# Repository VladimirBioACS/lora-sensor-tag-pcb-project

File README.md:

# LoRa Sensor TAG

Simple LoRa humidity and temperature monitoring device, based on the ESP32-Wroom-D SoC module.
Repo contains KiCAD 10 project for LoRa Sensor TAG device with external component libs.

## Project description

The architecture of the project is described with the diagram below (lora_sensor_tag_architecture.jpg):

The LoRa Sensor Project is designed to create a network of low-power, long-range sensors for environmental monitoring. 
The project aims to leverage LoRa technology to enable efficient data collection from remote locations, 
providing real-time insights into various environmental parameters such as temperature and humidity. The LoRa modem works
within 433 Mhz LF baseband.

It is developed simply for the educational purpose, aiming to provide students and hobbyists with hands-on experience in 
building and managing a LoRa-based sensor network.

The device composed of several key components:

- A LoRa module for long-range wireless communication.
- Sensor for measuring environmental parameters such as temperature and humidity.
- A microcontroller to process sensor data and manage communication.
- A power source (li-ion battery) with DC-DC buck-boost converter and LDO to manage power supply and ensure stable operation.
- Auxiliary components such as USB-UART bridge for serial communication and programming the microcontroller.

The following key components were used:

- MAX17048G_T10 - Fuel Gauge IC to monitor battery status
- MCP73871-2CAI_ML - Li-Ion/Li-Polymer Battery Charger to manage battery charging and protection
- SHT20 - Temperature and Humidity Sensor to measure environmental conditions
- SX1276IMLTRT - LoRa Transceiver Module to enable long-range wireless communication
- PE4259 - RF switch for LoRa antenna
- TPS63070RNMR - Buck-Boost Converter to manage power supply and ensure stable operation
- ESP32 - Microcontroller to process sensor data and manage communication
- CP2102 - USB to UART Bridge Controller to enable serial communication between the microcontroller and a computer. Also, acts as a programmer for the microcontroller.

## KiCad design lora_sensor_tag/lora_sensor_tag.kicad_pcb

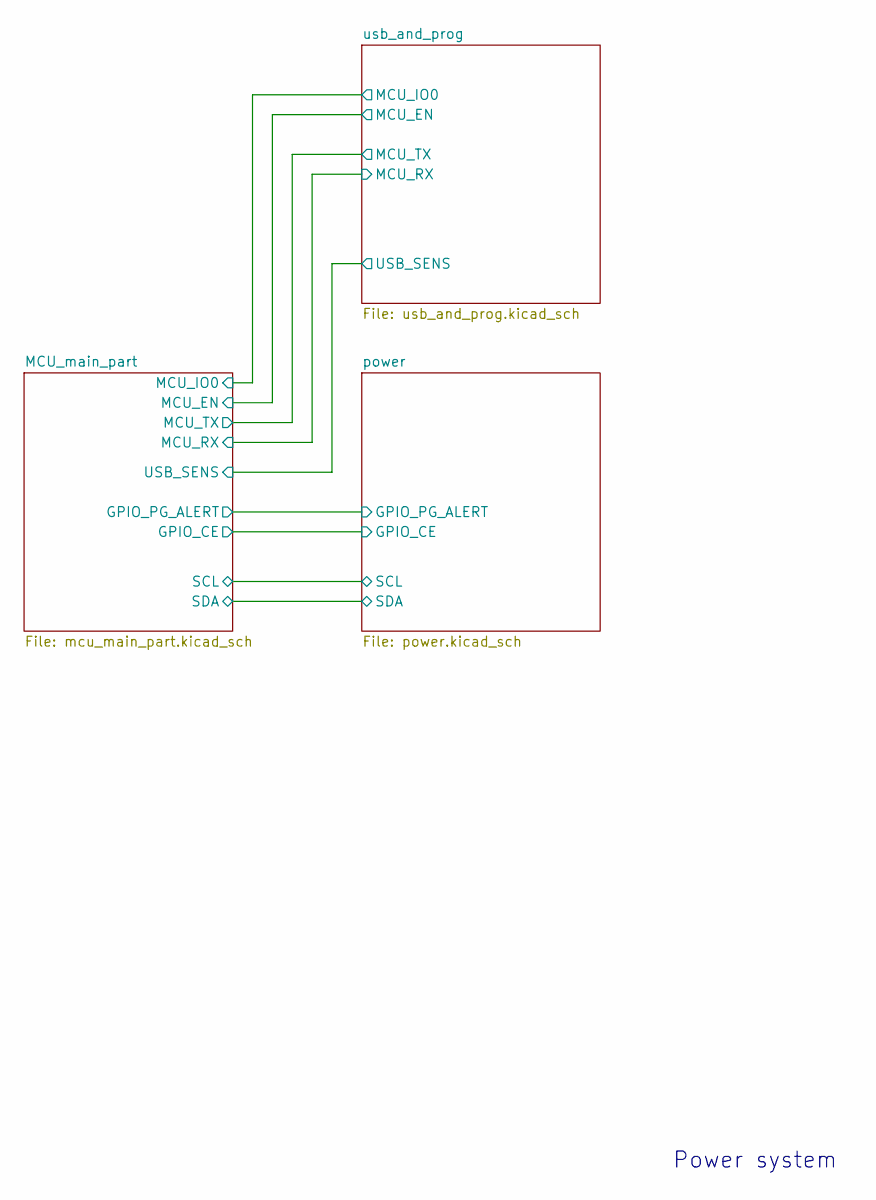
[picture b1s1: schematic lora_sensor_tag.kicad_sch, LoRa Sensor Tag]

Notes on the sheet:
Power system

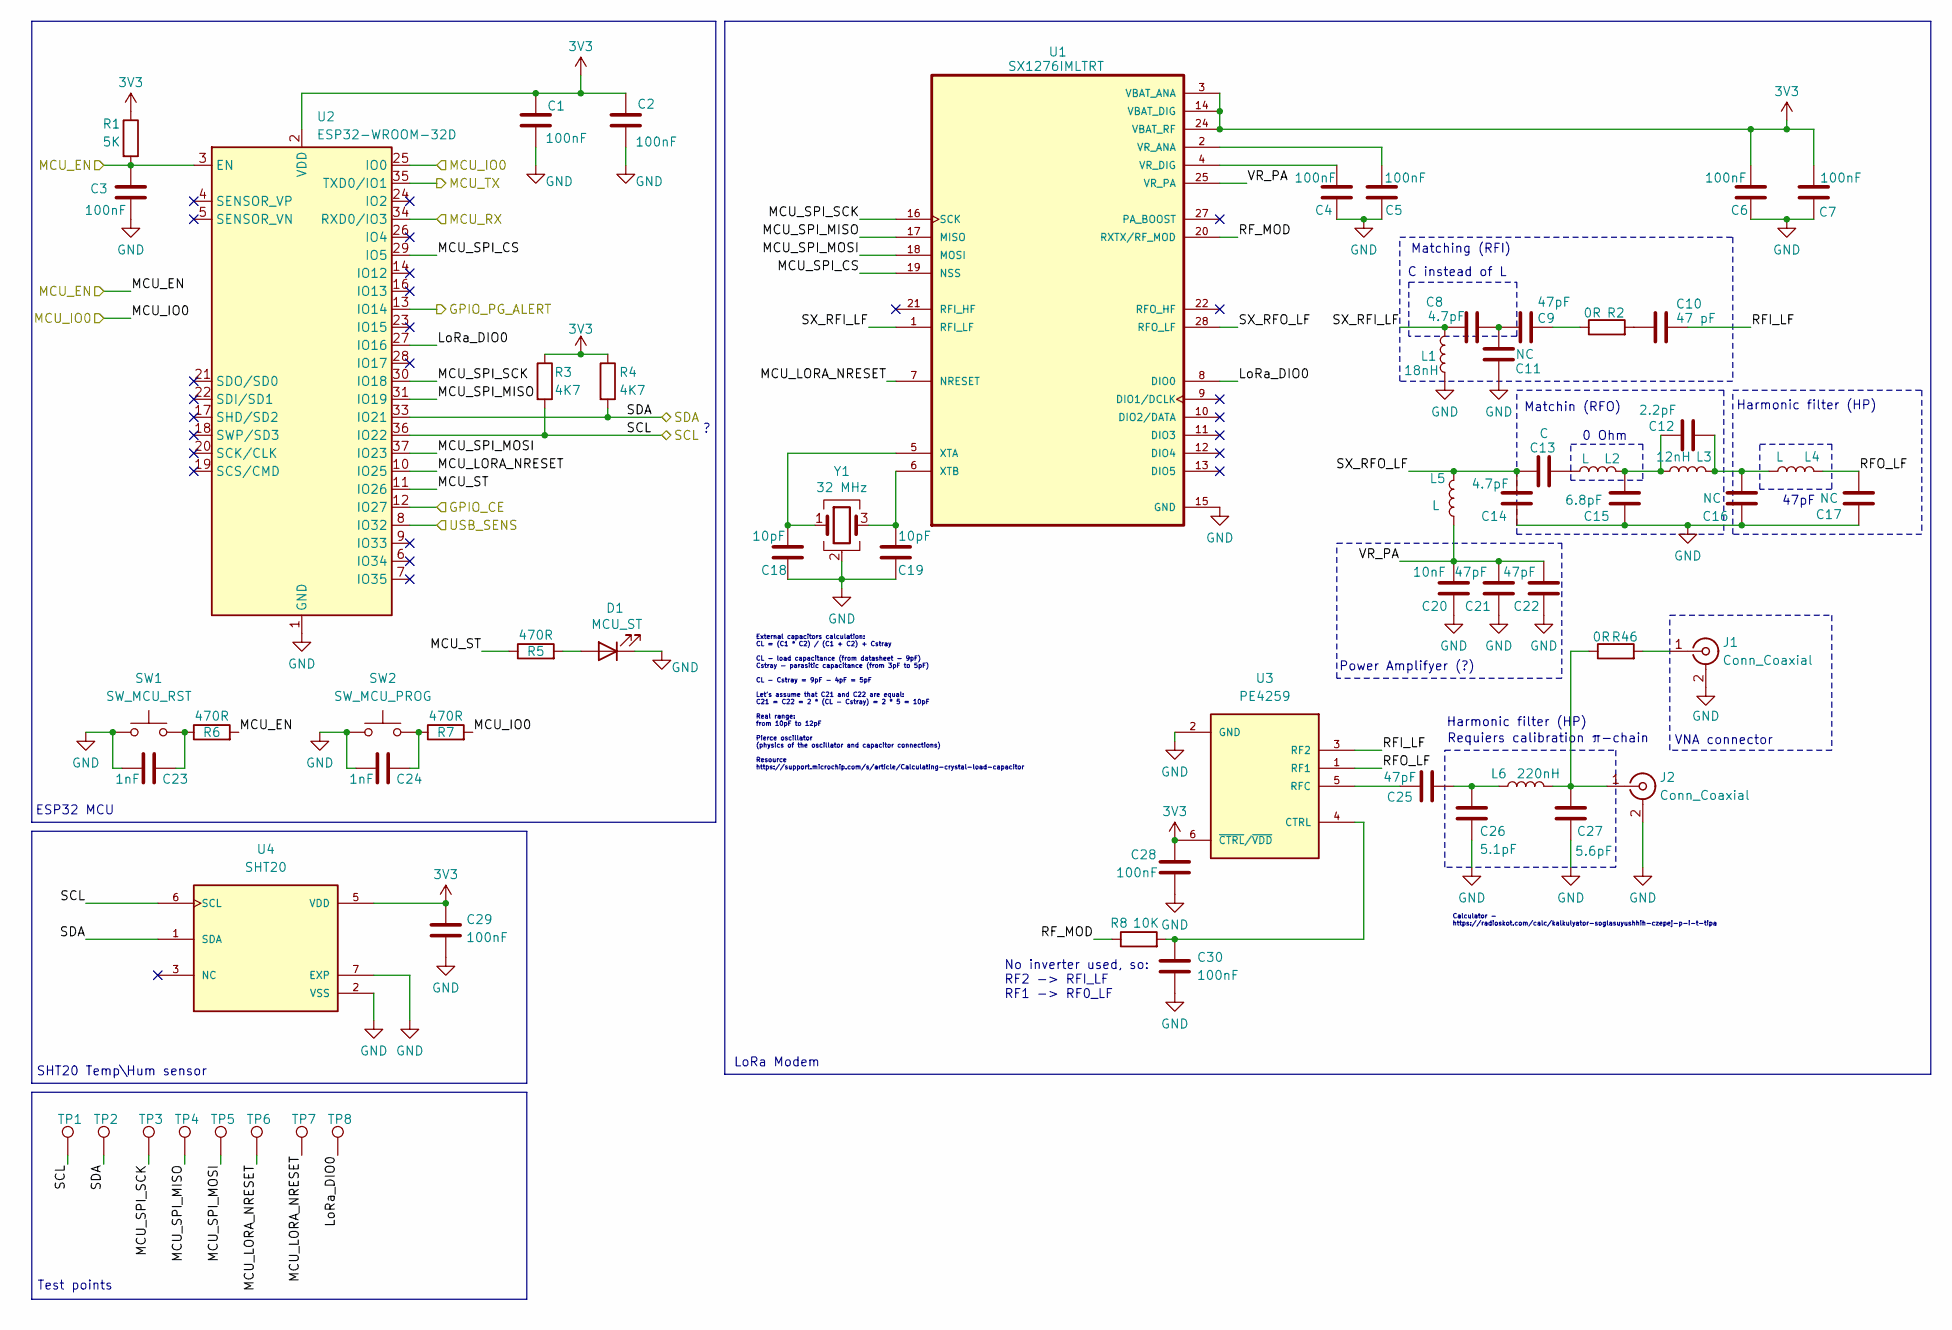
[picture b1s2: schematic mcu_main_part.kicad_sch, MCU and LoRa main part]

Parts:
C1, C2, C3, C4, C5, C6, C7, C28, C29, C30: 100nF; C_0603_1608Metric
C8, C14: 4.7pF; C_0402_1005Metric
C9, C21, C22, C25: 47pF; C_0402_1005Metric
C10: 47 pF; C_0402_1005Metric
C11, C16, C17: NC; C_0402_1005Metric
C12: 2.2pF; C_0402_1005Metric
C13: C; C_0402_1005Metric
C15: 6.8pF; C_0402_1005Metric
C18, C19: 10pF; C_0603_1608Metric
C20: 10nF; C_0402_1005Metric
C23, C24: 1nF; C_0603_1608Metric
C26: 5.1pF; C_0402_1005Metric
C27: 5.6pF; C_0402_1005Metric
D1: MCU_ST; LED_0603_1608Metric
J1, J2: Conn_Coaxial; SMA_BAT_Wireless_BWSMA-KWE-Z001
L1: 18nH; L_0402_1005Metric
L2: L; R_0402_1005Metric
L3: 12nH; L_0402_1005Metric
L4: L; C_0402_1005Metric
L5: L; L_0402_1005Metric
L6: 220nH; L_0402_1005Metric
R1: 5K; R_0603_1608Metric
R2: 0R; R_0603_1608Metric
R3, R4: 4K7; R_0603_1608Metric
R5, R6, R7: 470R; R_0603_1608Metric
R8: 10K; R_0603_1608Metric
R46: 0R; R_0402_1005Metric
SW1: SW_MCU_RST; SW_Push_1TS009xxxx-xxxx-xxxx_6x6x5mm
SW2: SW_MCU_PROG; SW_Push_1TS009xxxx-xxxx-xxxx_6x6x5mm
TP1, TP2, TP3, TP4, TP5, TP6, TP7, TP8: TestPoint; TestPoint_Pad_D1.0mm
U1: SX1276IMLTRT; QFN65P600X600X100-29N; PARTREV 5
U2: ESP32-WROOM-32D
U3: PE4259; SOT65P215X110-6N
U4: SHT20; XDCR_SHT20; PARTREV 4
Y1: 32 MHz; Crystal_SMD_3225-4Pin_3.2x2.5mm

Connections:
3V3: C1.1, C2.1, C6.1, C7.1, C28.1, C29.1, R1.1, R3.1, R4.1, U1.3 (VBAT_ANA), U1.14 (VBAT_DIG), U1.24 (VBAT_RF), U2.2 (VDD), U3.6 (~CTRL/~VDD), U4.5 (VDD); also elsewhere on the board
/MCU_main_part/GPIO_CE: U2.12 (IO27); also elsewhere on the board
/MCU_main_part/GPIO_PG_ALERT: U2.13 (IO14); also elsewhere on the board
/MCU_main_part/LoRa_DIO0: TP8.1 (1_1), U1.8 (DIO0), U2.27 (IO16)
/MCU_main_part/MCU_EN: C3.1, R1.2, R6.2, U2.3 (EN); also elsewhere on the board
/MCU_main_part/MCU_IO0: R7.2, U2.25 (IO0); also elsewhere on the board
/MCU_main_part/MCU_LORA_NRESET: TP6.1 (1_1), TP7.1 (1_1), U1.7 (NRESET), U2.10 (IO25)
/MCU_main_part/MCU_SPI_CS: U1.19 (NSS), U2.29 (IO5)
/MCU_main_part/MCU_SPI_MISO: TP4.1 (1_1), U1.17 (MISO), U2.31 (IO19)
/MCU_main_part/MCU_SPI_MOSI: TP5.1 (1_1), U1.18 (MOSI), U2.37 (IO23)
/MCU_main_part/MCU_SPI_SCK: TP3.1 (1_1), U1.16 (SCK), U2.30 (IO18)
/MCU_main_part/MCU_ST: R5.1, U2.11 (IO26)
/MCU_main_part/RFI_LF: C10.2, U3.3 (RF2)
/MCU_main_part/RFO_LF: C17.1, L4.2, U3.1 (RF1)
/MCU_main_part/RF_MOD: R8.1, U1.20 (RXTX/RF_MOD)
/MCU_main_part/SCL: R3.2, TP1.1 (1_1), U2.36 (IO22), U4.6 (SCL); also elsewhere on the board
/MCU_main_part/SDA: R4.2, TP2.1 (1_1), U2.33 (IO21), U4.1 (SDA); also elsewhere on the board
/MCU_main_part/SX_RFI_LF: C8.1, L1.2, U1.1 (RFI_LF)
/MCU_main_part/SX_RFO_LF: C13.2, C14.1, L5.2, U1.28 (RFO_LF)
/MCU_main_part/USB_SENS: U2.8 (IO32); also elsewhere on the board
/MCU_main_part/VR_PA: C20.1, C21.1, C22.1, L5.1, U1.25 (VR_PA)
/usb_and_prog/RX: U2.34 (RXD0/IO3); also elsewhere on the board
/usb_and_prog/TX: U2.35 (TXD0/IO1); also elsewhere on the board
GND: C1.2, C2.2, C3.2, C4.2, C5.2, C6.2, C7.2, C11.2, C14.2, C15.2, C16.2, C17.2, C18.2, C19.2, C20.2, C21.2, C22.2, C23.1, C24.1, C26.1, C27.1, C28.2, C29.2, C30.1, D1.1 (K), J1.2 (Ext), J2.2 (Ext), L1.1, SW1.1, SW2.1, U1.15 (GND), U1.23 (GND), U1.26 (GND), U1.29 (GND), U2.1 (GND), U2.15 (GND), U2.38 (GND), U2.39 (GND), U3.2 (GND), U4.2 (VSS), U4.7 (EXP), Y1.2 (G), Y1.4 (G); also elsewhere on the board
unnamed: C9.2, R2.1
unnamed: C10.1, R2.2
unnamed: C8.2, C9.1, C11.1
unnamed: C12.1, C16.1, L3.2, L4.1
unnamed: C12.2, C15.1, L2.2, L3.1
unnamed: C13.1, L2.1
unnamed: C23.2, R6.1, SW1.2
unnamed: C24.2, R7.1, SW2.2
unnamed: C25.2, C26.2, L6.1
unnamed: D1.2 (A), R5.2
unnamed: J1.1 (In), R46.2
unnamed: C27.2, J2.1 (In), L6.2, R46.1
unnamed: C5.1, U1.2 (VR_ANA)
unnamed: C4.1, U1.4 (VR_DIG)
unnamed: C18.1, U1.5 (XTA), Y1.1
unnamed: C19.1, U1.6 (XTB), Y1.3
unnamed: C30.2, R8.2, U3.4 (CTRL)
unnamed: C25.1, U3.5 (RFC)

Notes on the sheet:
SHT20 Temp\Hum sensor
External capacitors calculation: CL = (C1 * C2) / (C1 + C2) + Cstray CL - load capacitance (from datasheet - 9pF) Cstray - parasitic capacitance (from 3pF to 5pF) CL - Cstray = 9pF - 4pF = 5pF Let's assume that C21 and C22 are equal: C21 = C22 = 2 * (CL - Cstray) = 2 * 5 = 10pF Real range: from 10p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
Requiers calibration π-chain
Harmonic filter (HP)
Test points
LoRa Modem
ESP32 MCU
0 Ohm
Matchin (RFO)
47pF
VNA connector
C instead of L
Power Amplifyer (?)
Calculator - https://radioskot.com/calc/kalkulyator-soglasuyushhih-czepej-p-i-t-tipa
Matching (RFI)
No inverter used, so: RF2 -> RFI_LF RF1 -> RF0_LF

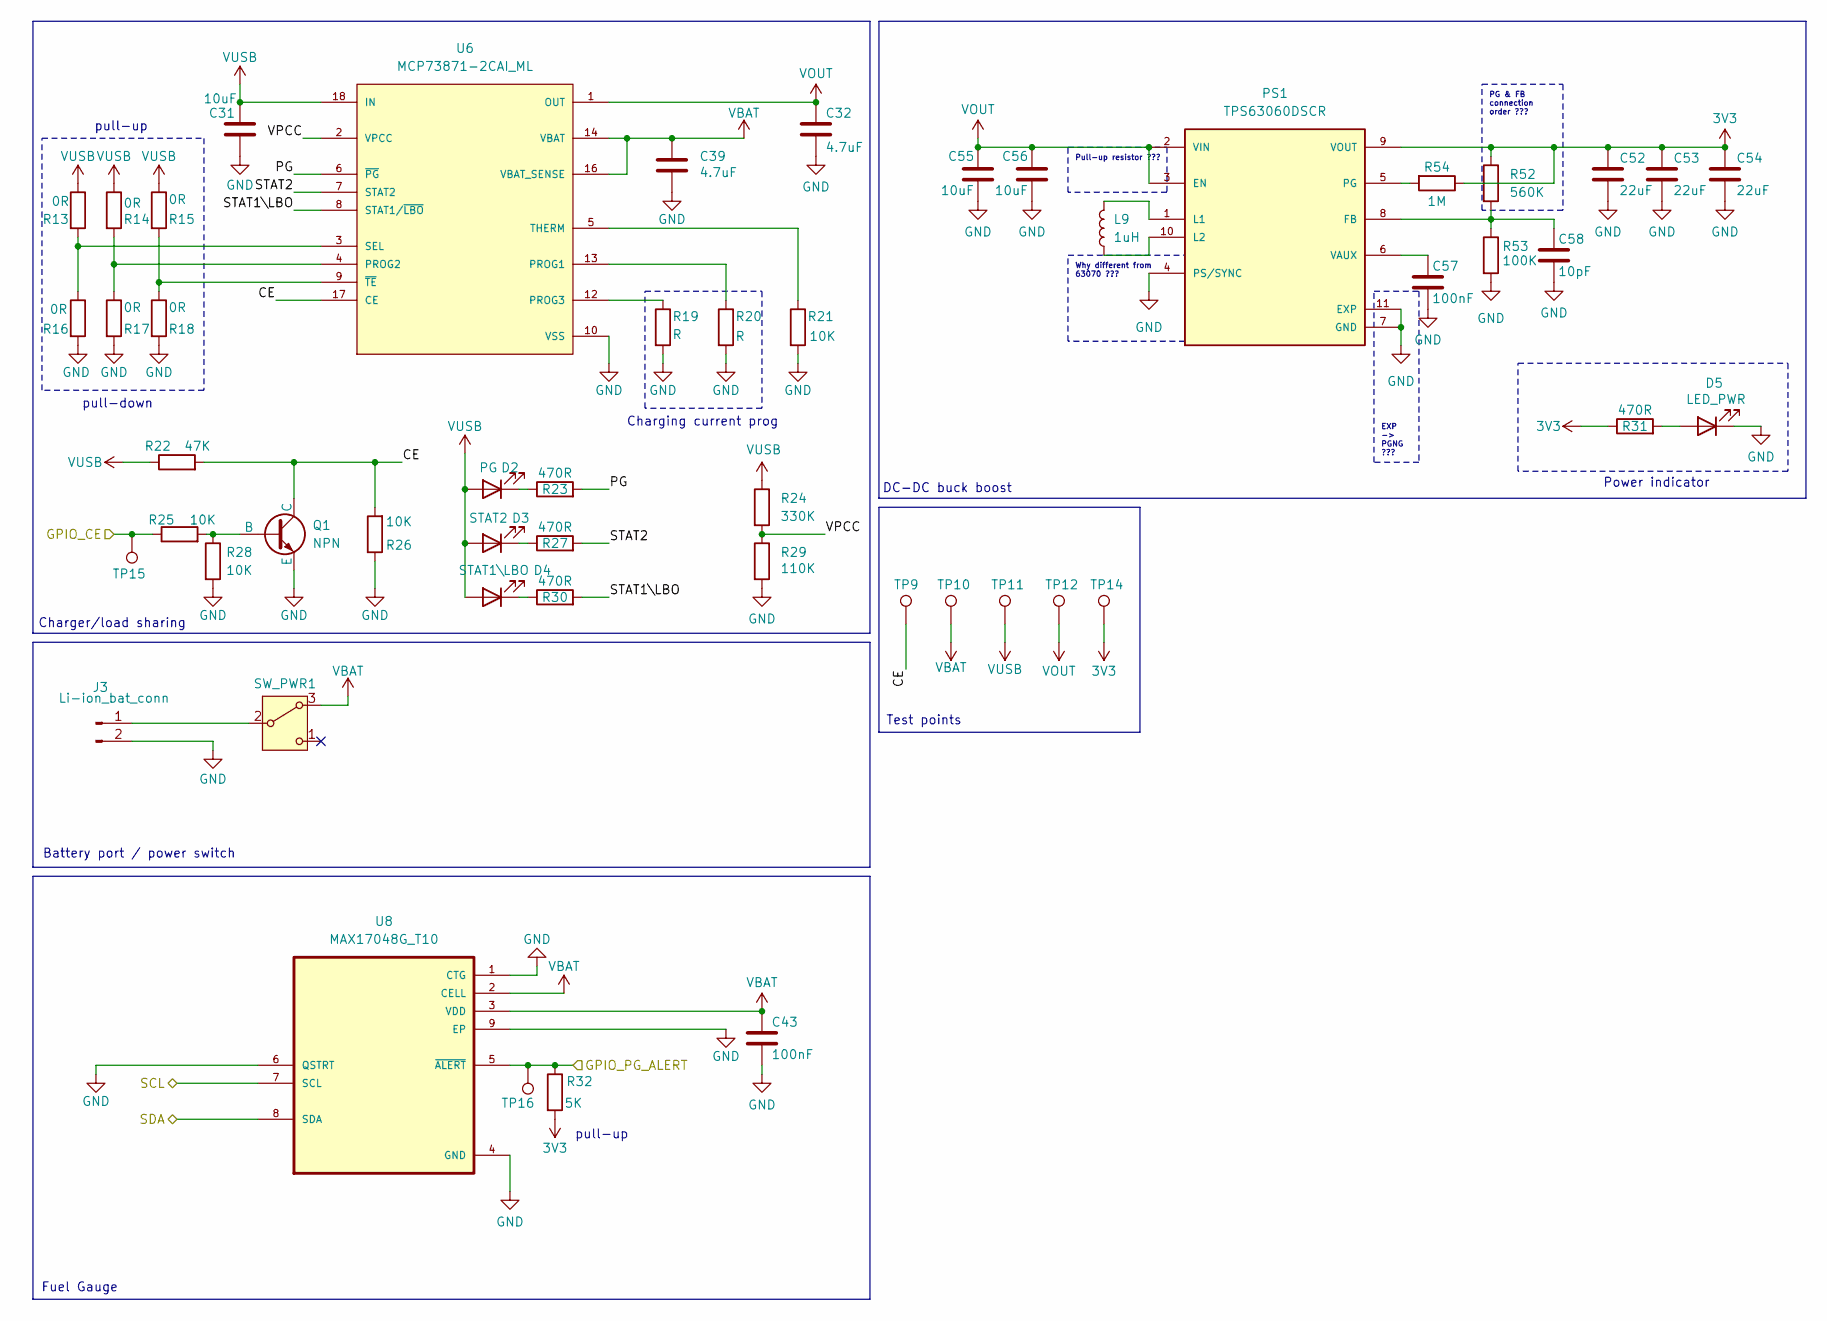
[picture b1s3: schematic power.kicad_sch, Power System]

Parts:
C31: 10uF; C_0603_1608Metric
C32, C39: 4.7uF; C_0603_1608Metric
C43: 100nF; C_0603_1608Metric
C52, C53, C54: 22uF; C_0805_2012Metric
C55, C56: 10uF; C_0805_2012Metric
C57: 100nF; C_0402_1005Metric
C58: 10pF; C_0603_1608Metric
D2: PG; LED_0603_1608Metric
D3: STAT2; LED_0603_1608Metric
D4: STAT1\LBO; LED_0603_1608Metric
D5: LED_PWR; LED_0603_1608Metric
J3: Li-ion_bat_conn; PinHeader_1x02_P2.54mm_Vertical
L9: 1uH; L_Coilcraft_XxL4020
PS1: TPS63060DSCR; CONV_TPS63060DSCR; PARTREV C
Q1: NPN; SOT-23
R13, R14, R15, R16, R17, R18: 0R; R_0603_1608Metric
R19, R20: R; R_0603_1608Metric
R21, R25, R26, R28: 10K; R_0603_1608Metric
R22: 47K; R_0603_1608Metric
R23, R27, R30, R31: 470R; R_0603_1608Metric
R24: 330K; R_0603_1608Metric
R29: 110K; R_0603_1608Metric
R32: 5K; R_0603_1608Metric
R52: 560K; R_0603_1608Metric
R53: 100K; R_0603_1608Metric
R54: 1M; R_0603_1608Metric
SW_PWR1: SW_Nidec_CAS-120A1; Nidec_Copal_CAS-120A
TP9, TP10, TP11, TP12, TP14, TP15, TP16: TestPoint; TestPoint_Pad_D1.0mm
U6: MCP73871-2CAI_ML; QFN50P400X400X100-21N; PARTREV D
U8: MAX17048G_T10; SON50P200X200X80-9N

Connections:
3V3: C52.1, C53.1, C54.1, PS1.9 (VOUT), R31.1, R32.2, R52.1, R54.1, TP14.1 (1_1); also elsewhere on the board
/MCU_main_part/GPIO_CE: R25.1, TP15.1 (1_1); also elsewhere on the board
/MCU_main_part/GPIO_PG_ALERT: R32.1, TP16.1 (1_1), U8.5 (~ALERT); also elsewhere on the board
/MCU_main_part/SCL: U8.7 (SCL); also elsewhere on the board
/MCU_main_part/SDA: U8.8 (SDA); also elsewhere on the board
/power/CE: Q1.1 (C), R22.2, R26.2, TP9.1 (1_1), U6.17 (CE)
/power/PG: R23.2, U6.6 (~PG)
/power/STAT1\LBO: R30.2, U6.8 (STAT1/~LBO)
/power/STAT2: R27.2, U6.7 (STAT2)
/power/VPCC: R24.2, R29.1, U6.2 (VPCC)
GND: C31.1, C32.2, C39.2, C43.2, C52.2, C53.2, C54.2, C55.2, C56.2, C57.2, C58.2, D5.1 (K), J3.2, PS1.4 (PS/SYNC), PS1.7 (GND), PS1.11 (EXP), Q1.3 (E), R16.2, R17.2, R18.2, R19.2, R20.2, R21.2, R26.1, R28.2, R29.2, R53.2, U6.10 (VSS), U6.11 (VSS), U6.21 (VSS), U8.1 (CTG), U8.4 (GND), U8.6 (QSTRT), U8.9 (EP); also elsewhere on the board
unnamed: D2.1 (K), R23.1
unnamed: D3.1 (K), R27.1
unnamed: D4.1 (K), R30.1
unnamed: D5.2 (A), R31.2
unnamed: J3.1, SW_PWR1.2 (B)
unnamed: C58.1, PS1.8 (FB), R52.2, R53.1
unnamed: L9.2, PS1.1 (L1)
unnamed: L9.1, PS1.10 (L2)
unnamed: PS1.5 (PG), R54.2
unnamed: C57.1, PS1.6 (VAUX)
unnamed: Q1.2 (B), R25.2, R28.1
unnamed: R20.1, U6.13 (PROG1)
unnamed: R14.2, R17.1, U6.4 (PROG2)
unnamed: R19.1, U6.12 (PROG3)
unnamed: R13.2, R16.1, U6.3 (SEL)
unnamed: R21.1, U6.5 (THERM)
unnamed: R15.2, R18.1, U6.9 (~TE)
VBAT: C39.1, C43.1, SW_PWR1.3 (A), TP10.1 (1_1), U6.14 (VBAT), U6.15 (VBAT), U6.16 (VBAT_SENSE), U8.2 (CELL), U8.3 (VDD)
VOUT: C32.1, C55.1, C56.1, PS1.2 (VIN), PS1.3 (EN), TP12.1 (1_1), U6.1 (OUT), U6.20 (OUT)
VUSB: C31.2, D2.2 (A), D3.2 (A), D4.2 (A), R13.1, R14.1, R15.1, R22.1, R24.1, TP11.1 (1_1), U6.18 (IN), U6.19 (IN); also elsewhere on the board

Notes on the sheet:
Charging current prog
pull-down
DC-DC buck boost
Power indicator
pull-up
Test points
Charger/load sharing
Battery port / power switch
Fuel Gauge
EXP -> PGNG ???
Why different from 63070 ???
Pull-up resistor ???
PG & FB connection order ???

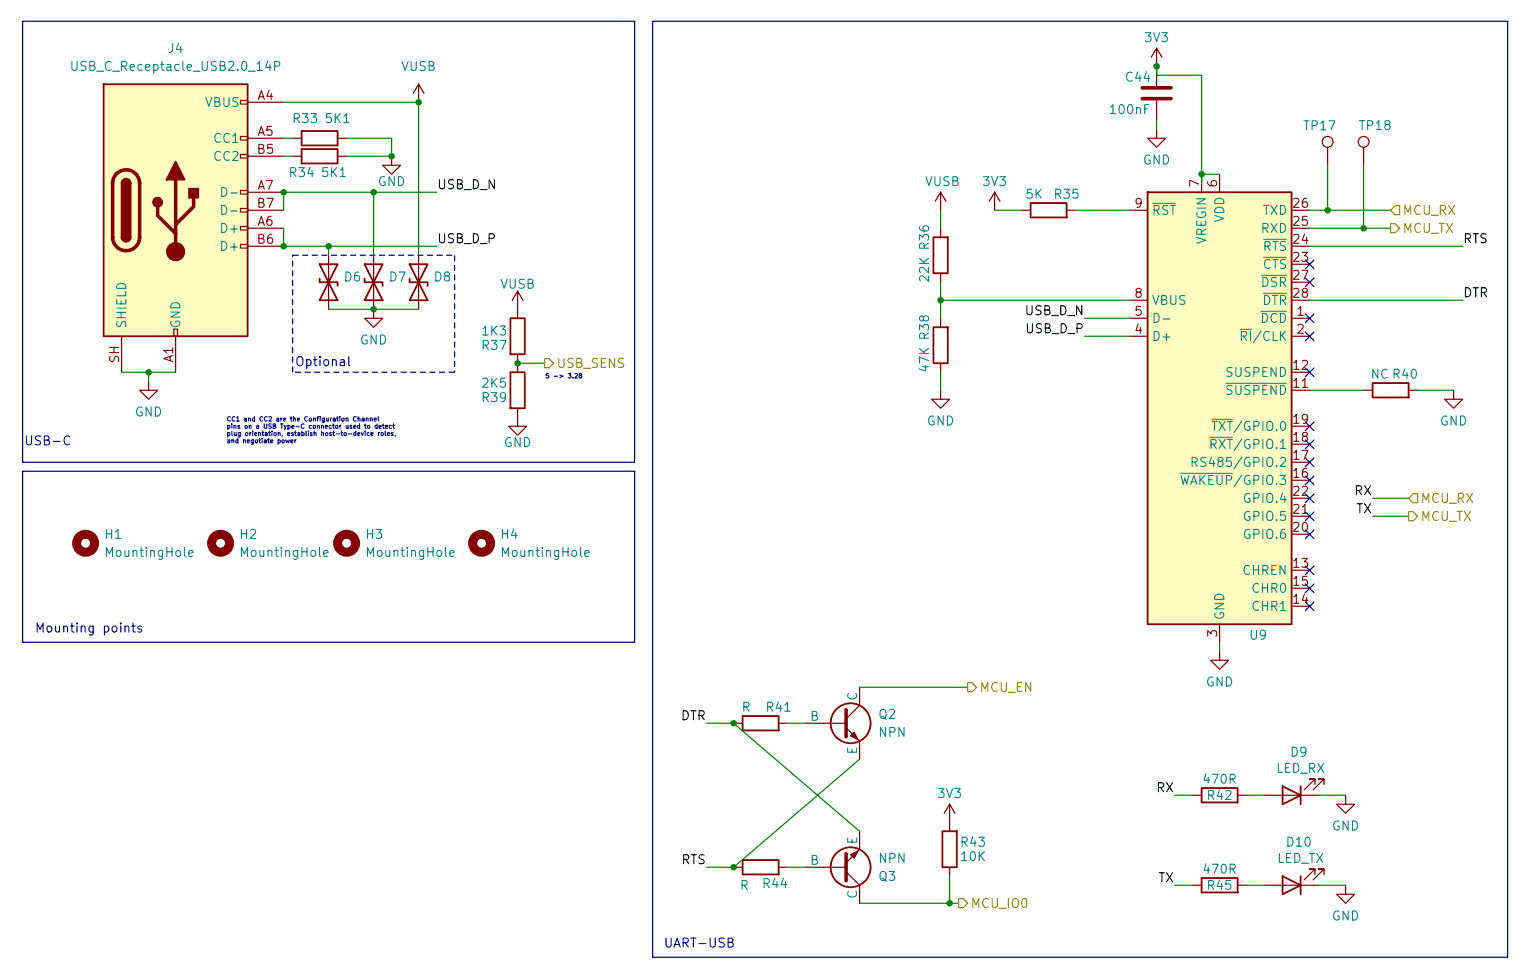
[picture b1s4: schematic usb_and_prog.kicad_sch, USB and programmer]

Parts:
C44: 100nF; C_0603_1608Metric
D6, D7, D8: 1N630xCA; D_0603_1608Metric
D9: LED_RX; LED_0603_1608Metric
D10: LED_TX; LED_0603_1608Metric
H1, H2, H3, H4: MountingHole; MountingHole_2.1mm
J4: USB_C_Receptacle_USB2.0_14P; USB_C_Receptacle_XKB_U262-16XN-4BVC11
Q2, Q3: NPN; SOT-23
R33, R34: 5K1; R_0603_1608Metric
R35: 5K; R_0603_1608Metric
R36: 22K; R_0603_1608Metric
R37: 1K3; R_0603_1608Metric
R38: 47K; R_0603_1608Metric
R39: 2K5; R_0603_1608Metric
R40: NC; R_0603_1608Metric
R41, R44: R; R_0603_1608Metric
R42, R45: 470R; R_0603_1608Metric
R43: 10K; R_0603_1608Metric
TP17, TP18: TestPoint; TestPoint_Pad_D1.0mm
U9: CP2102N-Axx-xQFN28; QFN-28-1EP_5x5mm_P0.5mm_EP3.35x3.35mm

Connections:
3V3: C44.1, R35.1, R43.2, U9.6 (VDD), U9.7 (VREGIN); also elsewhere on the board
/MCU_main_part/MCU_EN: Q2.1 (C); also elsewhere on the board
/MCU_main_part/MCU_IO0: Q3.1 (C), R43.1; also elsewhere on the board
/MCU_main_part/USB_SENS: R37.2, R39.1; also elsewhere on the board
/usb_and_prog/DTR: Q3.3 (E), R41.1, U9.28 (~DTR)
/usb_and_prog/RTS: Q2.3 (E), R44.1, U9.24 (~RTS)
/usb_and_prog/RX: R42.1, TP17.1 (1_1), U9.26 (TXD); also elsewhere on the board
/usb_and_prog/TX: R45.1, TP18.1 (1_1), U9.25 (RXD); also elsewhere on the board
/usb_and_prog/USB_D_N: D7.2 (A2), J4.A7 (D-), J4.B7 (D-), U9.5 (D-)
/usb_and_prog/USB_D_P: D6.2 (A2), J4.A6 (D+), J4.B6 (D+), U9.4 (D+)
GND: C44.2, D6.1 (A1), D7.1 (A1), D8.1 (A1), D9.1 (K), D10.1 (K), J4.A1 (GND), J4.A12 (GND), J4.B1 (GND), J4.B12 (GND), J4.SH (SHIELD), R33.1, R34.1, R38.1, R39.2, R40.2, U9.3 (GND), U9.29 (GND); also elsewhere on the board
unnamed: D9.2 (A), R42.2
unnamed: D10.2 (A), R45.2
unnamed: J4.A5 (CC1), R33.2
unnamed: J4.B5 (CC2), R34.2
unnamed: Q2.2 (B), R41.2
unnamed: Q3.2 (B), R44.2
unnamed: R36.1, R38.2, U9.8 (VBUS)
unnamed: R35.2, U9.9 (~RST)
unnamed: R40.1, U9.11 (~SUSPEND)
VUSB: D8.2 (A2), J4.A4 (VBUS), J4.A9 (VBUS), J4.B4 (VBUS), J4.B9 (VBUS), R36.2, R37.1; also elsewhere on the board

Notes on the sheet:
Mounting points
USB-C
5 -> 3.28
Optional
UART-USB
CC1 and CC2 are the Configuration Channel pins on a USB Type-C connector used to detect plug orientation, establish host-to-device roles, and negotiate power

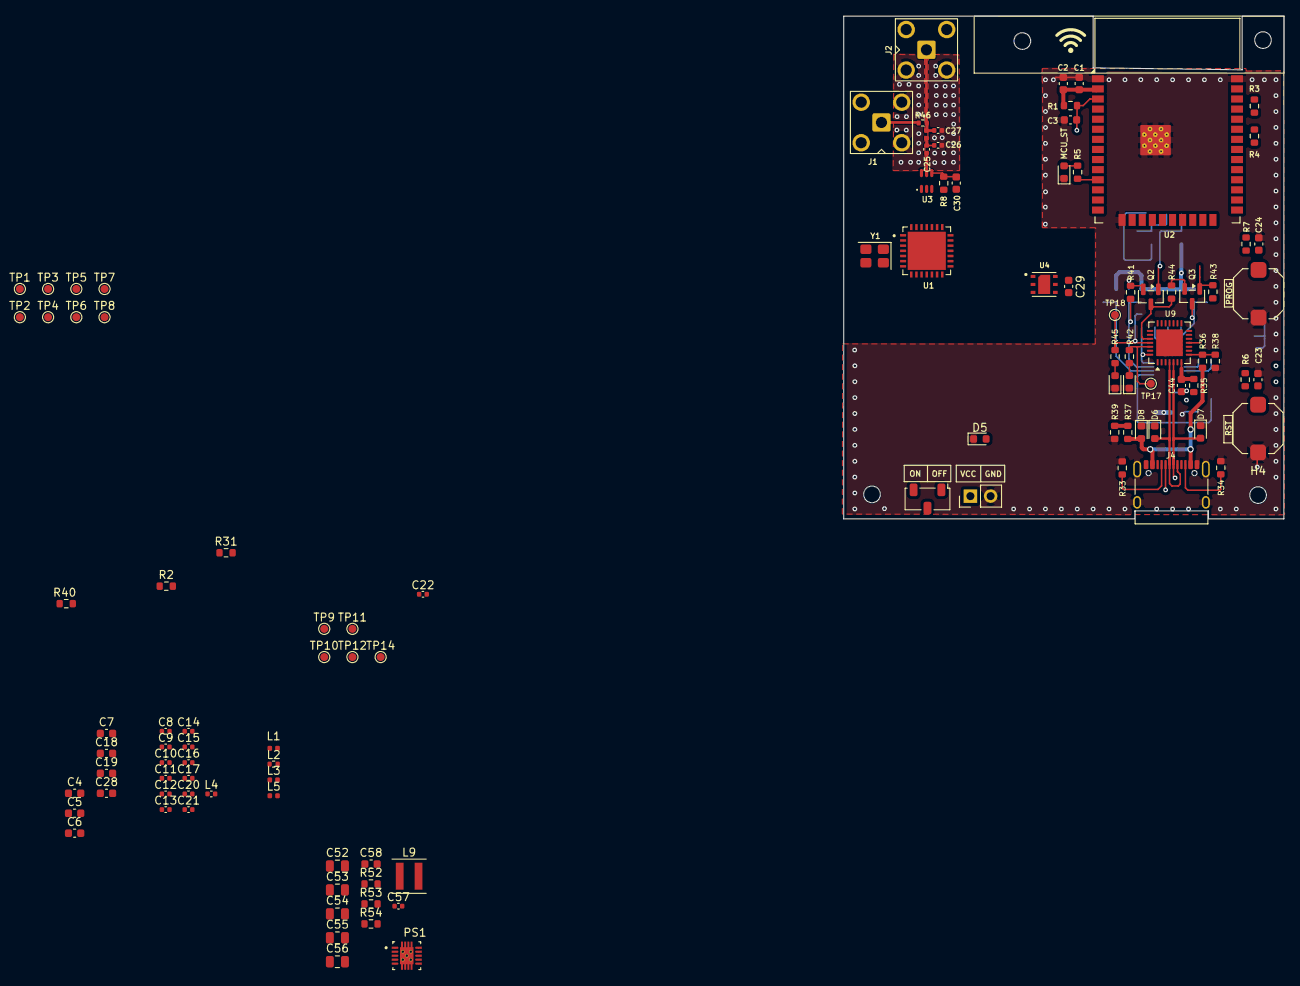
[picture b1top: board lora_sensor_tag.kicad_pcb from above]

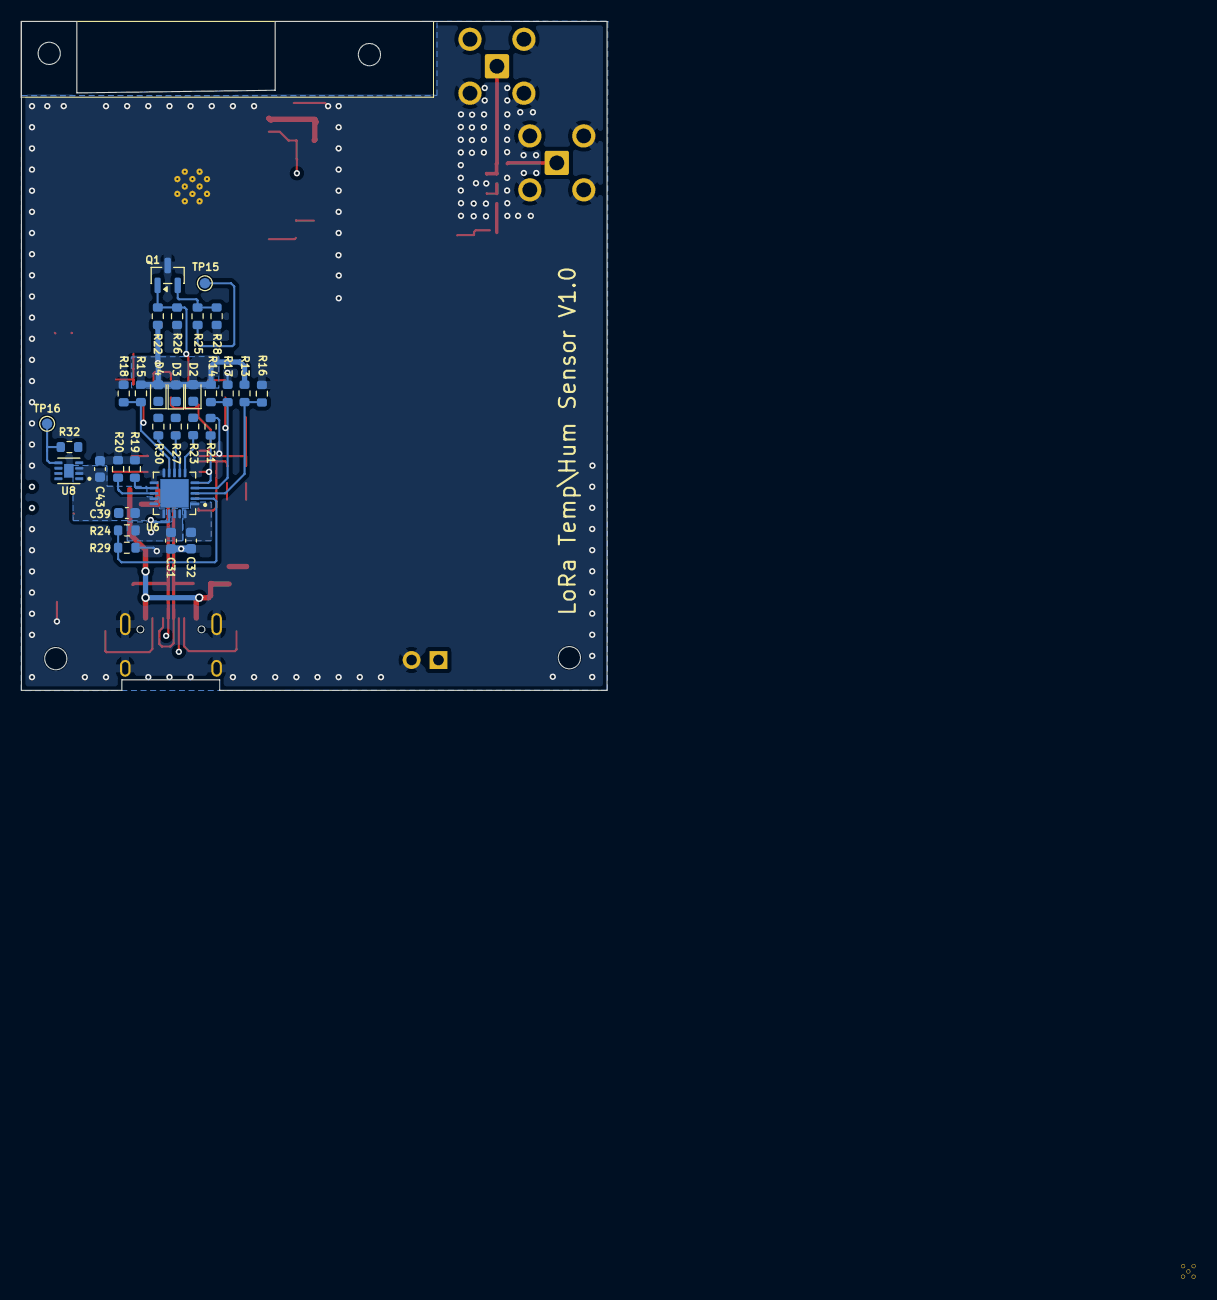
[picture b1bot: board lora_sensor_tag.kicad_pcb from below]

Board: 4 copper layers, 55.4 x 63.3 mm, 144 parts (31 on the bottom side), 80 nets.
